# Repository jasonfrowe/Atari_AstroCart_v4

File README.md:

# AstroCart V4: an Atari 7800 multicart on a Tang Nano 9K

AstroCart is a cartridge for the Atari 7800 built around a Sipeed Tang Nano
9K FPGA board. It starts in a menu, lists the `.a78` files on a microSD
card, and runs the one you pick. It also has a High Score Cart, POKEY sound,
and a fixed-point math unit for new programs.

It runs on the AstroCart_V2 circuit board with two hand modifications
([docs/HARDWARE.md](docs/HARDWARE.md)); the next board revision is in
[pcb/](pcb/README.md).

| | |
|---|---|
| [docs/MATHUNIT.md](docs/MATHUNIT.md) | the math unit: registers, accuracy, examples, demos |
| [docs/HARDWARE.md](docs/HARDWARE.md) | the board, the two modifications, pins |
| [docs/DEVELOPMENT.md](docs/DEVELOPMENT.md) | how it works inside, and the history of getting it to work |
| [pcb/README.md](pcb/README.md) | the KiCad project and the changes for the next board |

## What it does

* **Menu.** Browses the card's directories; file names are the titles.
  Up / down move, left / right page, fire opens a directory or starts a
  game. Two lines show the selected file's title, size, mapper, POKEY and TV
  system from its header.
* **SD card.** FAT32, with or without a partition table (MBR or GPT), long
  file names, any directory depth.
* **Cart types**, chosen from the `.a78` header:
  * linear ROM, 8K to 48K, with or without 16K RAM at `$4000`
  * SuperGame up to 512K: plain, with RAM, or with ROM at `$4000`
  * SuperGame up to 255 banks (4 MB), for the 528K and 1024K carts
  * Absolute (F-18 Hornet)
  * Activision (Double Dragon, Rampage), both dump orders
  * mirror RAM
* **POKEY** at `$4000`, `$0450`, `$0800` or `$0440`, and two POKEYs at
  `$0450` + `$0440`.
* **High Score Cart.** Its ROM and RAM come from the card, and the scores are
  written back to the card.
* **Math unit.** For programs written for this cart: 16 x 16 multiply,
  32 / 16 divide, square root, a 32-bit accumulator, a random byte, and a
  trig block (turn a vector by an angle; the angle and length of a vector).
  See [docs/MATHUNIT.md](docs/MATHUNIT.md).
* **Loading over USB.** A game can be sent straight from a computer instead
  of from the card, with bus statistics and a bus trace for debugging.

## What it does not do

* **Other cart hardware:** banked RAM, SOUPER, banksets, YM2151, COVOX and
  the XM are not implemented. Such a file shows NOT SUPPORTED in the menu.
* **Return to the menu from a game.** The way back is to power-cycle the
  FPGA: console off and USB unplugged, or reload the bitstream. A console
  power cycle alone restarts the game if USB keeps the FPGA running.
* **Saves** other than the High Score Cart's.
* **exFAT.** Cards over 32 GB usually come formatted that way; reformat
  them as FAT32.
* **More than 255 entries in one directory.** The first 255 found are shown.
  Titles are cut to 32 characters.
* **PAL** has not been tried: all testing was with NTSC files.
* **POKEY** is the sound half of the chip only, and its pitch has not been
  compared against a real one.

## What you need

To use it:

* An AstroCart_V2 board with the two modifications in
  [docs/HARDWARE.md](docs/HARDWARE.md), and a Tang Nano 9K.
* A microSD card, FAT32.
* [openFPGALoader](https://github.com/trabucayre/openFPGALoader) to put the
  bitstream on the Tang Nano (`brew install openfpgaloader` on a Mac), and a
  USB-C cable.
* A bitstream: `devcart.fs` from this repository's GitHub releases, or built
  as below.

To build it and to work on it:

| Software | Used for | Where the scripts look |
|---|---|---|
| [Gowin IDE](https://www.gowinsemi.com/en/support/download_eda/) (Education edition is enough for the GW1NR-9) | the bitstream | `GOWIN_BIN`, default `/Applications/GowinIDE.app/Contents/Resources/Gowin_EDA/IDE/bin` |
| [7800basic](https://github.com/7800-devtools/7800basic) (a release; it includes `dasm`) | the menu ROM, the demos, the math self-test | `bas7800dir`, default `~/Software/Atari7800/7800basic` |
| Python 3 | every tool in `tools/` (standard library only) | `python3` |
| openFPGALoader | loading and flashing | `openFPGALoader` |
| [Verilator](https://verilator.org) 5 and a C++ compiler | the simulations in `sim/` | `verilator` |
| The [a7800 fork](https://github.com/jasonfrowe/a7800) (MAME-based, with the math unit) | running math-unit programs in an emulator; the demos' and self-test's `run_emu.sh` | `A7800`, default `~/Software/a7800/mame64` |
| [KiCad](https://www.kicad.org) 9 | the board in `pcb/` | |

Only the first four are needed to build and load the cart. The serial tools
use a POSIX serial port (macOS or Linux).

## Getting started

1. **Put the bitstream in the Tang Nano's flash** (once; console off):

   ```bash
   openFPGALoader -b tangnano9k -f devcart.fs
   ```

2. **Prepare the card.** Copy `.a78` files (with their 128-byte headers)
   anywhere on a FAT32 card, in any directories.

3. **For high scores**, add the High Score Cart's two files. You supply the
   HSC ROM as an `.a78` file (128 + 4096 bytes):

   ```bash
   python3 tools/mkhsc.py "High Score Cartridge.a78" OUTDIR
   ```

   and copy `OUTDIR/ASTROCART` to the root of the card. It holds `HSC.A78`
   (the ROM) and `HSC.SAV` (the scores, 2K). An existing `HSC.SAV` is kept.

4. **Card in the Tang Nano, cart in the console, power on.** The menu shows
   "READING THE SD CARD", then the root directory.

LEDs on the Tang Nano (lit = on): 0 heartbeat, 1 cart enabled, 2 loading,
3 HALT pulled recently, 4 PHI2 activity, 5 HALT (DMA) activity.

## Building

```bash
./build.sh                    # build the menu ROM and the bitstream
./build.sh sram               # build, then load into the FPGA's SRAM
./build.sh flash              # build, then write to the FPGA's flash
./build.sh sram  --no-build   # load the bitstream that is already built
./build.sh flash --no-build
```

* **SRAM** is for trying a build: a few seconds, and gone when the FPGA
  loses power (USB unplugged and console off). The FPGA then starts from
  whatever is in flash.
* **Flash** is for the build to keep: loaded at every power-on, so the cart
  works without USB. Writing takes about half a minute.
* Either way the cart restarts in the menu, so switch the console off first.

The bitstream is `hw/devcart/build/impl/pnr/devcart.fs`. The build tries
placement seeds until one meets timing (a few minutes each), because the
FPGA is nearly full; if none does, it removes the bitstream instead of
leaving a bad one. `SEEDS="3 4 5" ./build.sh` chooses the seeds.

The steps by hand:

```bash
menu/build.sh                 # 7800basic -> menu/build/menu.bin (goes into the bitstream)
hw/devcart/build_clean.sh     # Gowin synthesis, place and route, seed sweep
openFPGALoader -b tangnano9k    hw/devcart/build/impl/pnr/devcart.fs    # SRAM
openFPGALoader -b tangnano9k -f hw/devcart/build/impl/pnr/devcart.fs    # flash
```

## Loading a cart over USB: devcart.py

`tools/devcart.py` talks to the cart over the Tang Nano's USB serial port
(230400 baud; it finds `/dev/cu.usbserial-*1` by itself, or `--port PATH`).
It sends a game from the computer, without the SD card:

```bash
python3 tools/devcart.py info GAME.a78     # how the header would be mapped; nothing is sent
```

1. Console **off**, USB connected, bitstream running.
2. `python3 tools/devcart.py load GAME.a78`
   The file goes into the cart's memory, is read back and compared, and the
   cart is switched on with that game in place of the menu. A 32K game
   takes about 2 seconds; the upload runs at about 23 kB a second.
3. Console on: the game starts. To change game: console off, `load` again.

The game stays loaded for as long as the FPGA has power, so the console can
be switched off and on. The math unit is enabled from the header just as the
menu does it. `load --no-halt` switches banks without stopping the 6502, as
games started from the menu do; without it the older stop-and-copy method is
used.

While a game runs:

```bash
python3 tools/devcart.py ident             # is the cart there? -> AC78V4 <enabled> <trace> <bank>
python3 tools/devcart.py stats             # bank switches, POKEY writes, High Score Cart saves, ...
python3 tools/devcart.py trace arm now     # record 512 bus cycles from now
python3 tools/devcart.py trace arm bank    #   ... or from the next bank switch
python3 tools/devcart.py trace dump FILE
python3 tools/devcart.py off               # stop driving the bus
```

With the console off, the card can be exercised from the computer the way
the menu does it:

```bash
python3 tools/devcart.py sd ls [DIR]                           # a directory, as the menu lists it
python3 tools/devcart.py sd load DIR/NAME --check GAME.a78     # load, start, compare with a local copy
```

`python3 tools/devcart.py --help` lists everything.

## Programs for the math unit

A program asks for the math unit with three bytes in its `.a78` header
(`tools/a78math.py FILE.a78` sets them). The definition, with examples, is
[docs/MATHUNIT.md](docs/MATHUNIT.md). The a7800 fork implements the same
unit bit for bit, so such programs can be developed in the emulator.

Five demos, in 7800basic with assembly for the arithmetic; each directory
has a README, and `demos/NAME/build.sh` makes `demos/NAME/build/NAME.a78`:

| | |
|---|---|
| `demos/galton` | a Galton board: balls, pegs and a bell curve |
| `demos/nbody` | gravity between up to four bodies, four scenarios |
| `demos/gas` | twelve discs in a box, and their speed distribution |
| `demos/spin` | a 3D point cloud turning in perspective (trig block) |
| `demos/orbit` | a game for two: launch probes at a moon round a star (trig block) |

`tests/mathtest` is the unit's self-test cart: 13,130 register checks against
the reference model, green screen for a pass.

## Tests without a console

```bash
(cd sim/math && make)              # the math unit's Verilog against its reference model
(cd sim/devcart && make)           # the cart: load, mappers, 6502 and MARIA-style traffic
(cd sim/multicart && make run)     # menu + SD card model + every mapper, 6502 code included (15 minutes)
(cd sim/pokey && make)             # POKEY
tests/mathtest/run_emu.sh          # the math self-test in the a7800 fork
```

`sim/multicart` loads the carts in `tests/carts`, and adds more cases if
Trebor's 7800 ROM PROPack is at `$PROPACK` (default
`~/Downloads/Trebors 7800 ROM PROPack v8_17`).

## Layout

```
rtl/cart/cart_bus.v      the 7800 bus: address filter, BRAM slots, write capture, bank switches
rtl/dev/devcart_top.v    top level: USB loader and commands, PSRAM-to-slot copy, menu registers
rtl/psram/               PSRAM controller, and both dies raced
rtl/sd/sd_spi.v          SD card, SPI mode
rtl/audio/               POKEY (sound) and PWM output
rtl/math/astromath.v     the math unit
menu/                    the menu: menu.bas (7800basic), fat.asm (card, FAT32, loader, launch)
hw/devcart/              pin constraints and the Gowin build
tools/                   devcart.py (USB), mkhsc.py, a78math.py, mkfat32.py (card images for tests)
sim/                     Verilator testbenches; sim/math/astromath.h is the math unit's reference model
tests/mathtest/          the math unit's self-test cart
tests/carts/             directory for test cart images (see tests/carts/README.md)
demos/                   programs for the math unit
lab/psram_lab/           the bitstream that characterised the PSRAM
pcb/                     KiCad project for the next board revision
docs/                    MATHUNIT, HARDWARE, DEVELOPMENT
```

## Licence

AstroCart V4 is free software under the GNU General Public License, version
3 or (at your option) any later version; see [LICENSE](LICENSE). It comes
with no warranty.

That covers what was written for this project: the Verilog in `rtl/`, the
menu, the tools, the simulations, the demos, the documents and the board in
`pcb/`. It does not cover third-party cart images
([tests/carts/README.md](tests/carts/README.md)), nor the pieces below that
came from elsewhere under their own terms.

## Credits

* **PSRAM controller.** `rtl/psram/psram_ll.v` is derived from Feng Zhou's
  (nand2mario) [PSRAM/HyperRAM controller for the Tang Nano
  9K](https://github.com/zf3/psram-tang-nano-9k), Apache License 2.0.
* **6502 for the simulation.** `sim/third_party/fake6502` is Fake6502 by Mike
  Chambers as modified by the [LLVM-MOS
  project](https://github.com/llvm-mos/llvm-mos-sdk), Apache License 2.0
  with LLVM exceptions; an unmodified copy, used only by `sim/multicart`.
* **7800basic** by Michael Saarna, derived from Fred Quimby's batari Basic:
  the menu and the demos are written in it, and assembled with the `dasm`
  it ships. `menu/gfx/menufont.png` is the `atascii.png` font from its
  samples. The built menu ROM inside the bitstream contains 7800basic's
  runtime (its 6502 code is CC0).
* **a7800**, the MAME-based Atari 7800 emulator by Mike Saarna and Robert
  Tuccitto: the mapper definitions here follow its source, and the
  [fork](https://github.com/jasonfrowe/a7800) with the math unit is how
  programs for it are developed.
* **POKEY.** `rtl/audio/pokey.v` was written for this project from the
  description in Avery Lee's Altirra Hardware Reference Manual.
* **Trebor's 7800 ROM PROPack** supplied the test files for the mappers
  beyond the eight in `tests/carts`.
* **Tools:** the Gowin EDA software, Verilator, openFPGALoader, KiCad.

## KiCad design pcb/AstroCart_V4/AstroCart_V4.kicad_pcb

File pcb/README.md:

# AstroCart PCB

`AstroCart_V4/` is the KiCad project for the V4 board revision. It builds
upon the original AstroCart_V2 board that development was done on,
incorporating the required hardware bodges and an audio filter improvement.

## Changes implemented in V4

The V2 prototype board required hand modifications to operate reliably. These
modifications, along with an audio low-pass filter component update, have been
incorporated into the V4 schematic and PCB layout:

| | V2 as drawn | V4 implementation |
|---|---|---|
| 1 | Q1 (BSS138) drain on cartridge pin 31 (`IRQ`) | Q1 drain routed to cartridge **pin 2 (`HALT`)**. In schematic/PCB, gate net is `/Q_HALT` (Tang Nano pin 83). Allows the FPGA to pull HALT low to stop the 6502 (e.g., during `devcart.py load`). |
| 2 | Q1 gate had no pull-down resistor (floated during FPGA configuration) | Added **R5 (10 kΩ, 0805)** from Q1 gate (`/Q_HALT`) to GND. Prevents Q1 from conducting and asserting HALT during console power-on reset. |
| 3 | Audio low-pass filter: R1 = 1 kΩ, C8 = 0.1 µF (cutoff ~1.6 kHz) | Updated **C8 to 10 nF** (with R1 = 1 kΩ), raising the low-pass cutoff to **~16 kHz**. Keeps audio clear without attenuating audible high frequencies while still filtering the 264 kHz PWM carrier. |

Background context, timing observations, and startup symptoms without the gate
pull-down are documented in [docs/HARDWARE.md](../docs/HARDWARE.md).

Since build 4, the cart does not pull HALT for games started from the menu
(bank switches are handled without stopping the 6502). Only `devcart.py load`
without `--no-halt` uses Q1. It remains on the board because it costs minimal
parts and provides the only mechanism for the cart to stop the 6502.

## Remaining suggestions for future revisions

Read from the schematic and from development findings. None of these are
strictly necessary for the cart to function as intended:

1. **A button for "back to the menu".** The only way back today is to
   power-cycle the FPGA. A push button on a free 3.3 V pin (Tang Nano pins
   68-75 are unconnected), reachable with the cart in the console, would let
   the bitstream do it. The Tang Nano's own buttons S1 and S2 (pins 4 and 3)
   could serve if they can be reached in the shell; a button on the board
   edge is easier to press. Needs RTL as well.
2. **A14 and A15 through U4.** A0-A13 come through SN74LVC245s on 3.3 V
   banks, A14 and A15 through the SN74LVC8T245 (U5) on the 1.8 V bank, so the
   two top address lines have different delays and thresholds from the rest;
   the bus logic waits for two equal samples because of it. U4 has two unused
   channels (A1/B1, A2/B2, inputs tied to ground now) and the Tang Nano has
   free 3.3 V pins, so all sixteen could take the same path. This changes
   the pin constraints, and the present arrangement works; do it only if the
   board is being re-routed there anyway.
3. **IRQ, if it is ever wanted** (POKEY interrupts, for example): its own
   BSS138 with a gate pull-down, on a free pin. U5's eighth channel (A8/B8)
   is free if the cart should also read the line.
4. **Test points** for PHI2, HALT, R/W, A15 and a data line at the cartridge
   edge: every timing question in this project was answered with a probe on
   those.

Things looked at and left alone: D2 (SS14) keeps USB power from back-feeding
the console; U5's B side and the 1.8 V regulator run from the console's 5 V
only, and the SN74LVC8T245 isolates its A side when that is off, so
USB-only operation on the bench is fine; R2 holds the data-bus driver off
until the FPGA is configured.

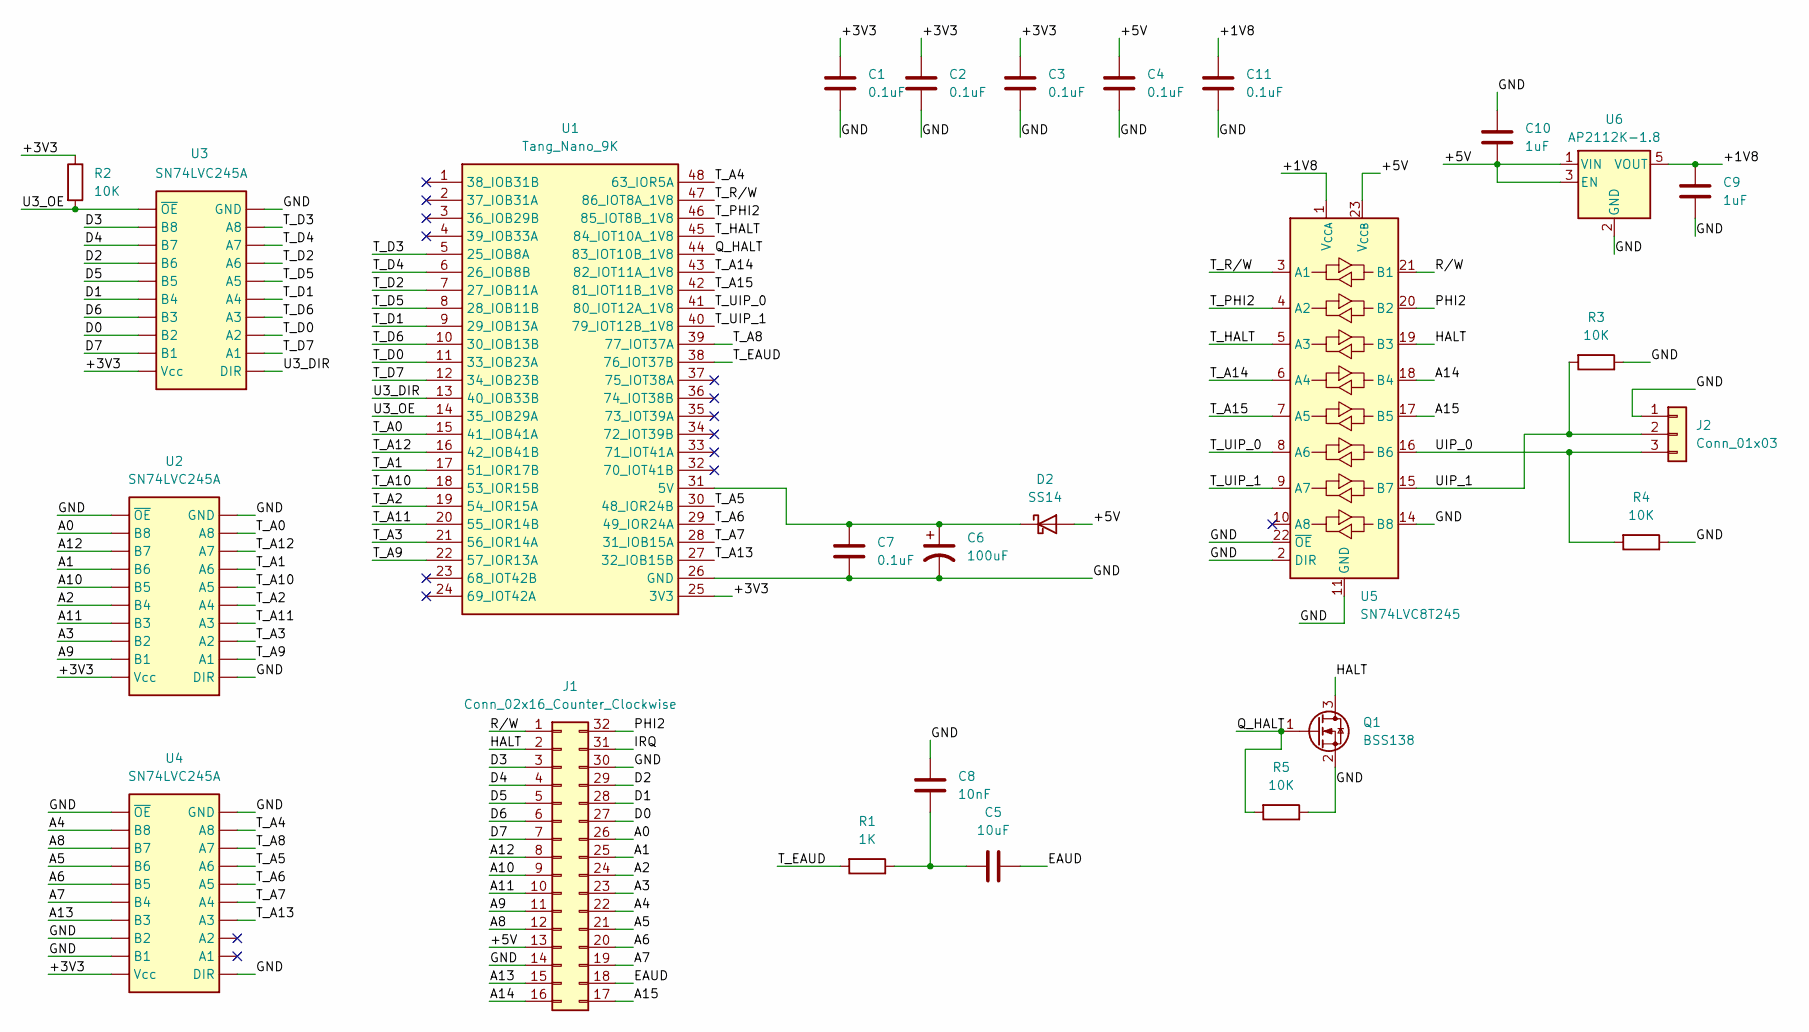
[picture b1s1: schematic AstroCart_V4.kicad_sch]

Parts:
C1, C2, C3, C4, C7, C11: 0.1uF; C_0805_2012Metric_Pad1.18x1.45mm_HandSolder
C5: 10uF; C_0805_2012Metric_Pad1.18x1.45mm_HandSolder
C6: 100uF; CP_Radial_D6.3mm_P2.50mm
C8: 10nF; C_0805_2012Metric_Pad1.18x1.45mm_HandSolder
C9, C10: 1uF; C_0805_2012Metric_Pad1.18x1.45mm_HandSolder
D2: SS14; D_SMA
J1: Conn_02x16_Counter_Clockwise; A7800
J2: Conn_01x03; JST_XH_B3B-XH-A_1x03_P2.50mm_Vertical
Q1: BSS138; SOT-23
R1: 1K; R_0805_2012Metric_Pad1.20x1.40mm_HandSolder
R2, R3, R4, R5: 10K; R_0805_2012Metric_Pad1.20x1.40mm_HandSolder
U1: Tang_Nano_9K; DIP-48_TangNano9K
U2, U3, U4: SN74LVC245A; SOIC-20W_7.5x12.8mm_P1.27mm
U5: SN74LVC8T245; SOIC-24W_7.5x15.4mm_P1.27mm
U6: AP2112K-1.8; SOT-23-5

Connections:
/+1V8: C9.2, C11.1, U5.1 (V_{CCA}), U6.5 (VOUT)
/+3V3: C1.1, C2.1, C3.1, R2.1, U1.25 (3V3), U2.20 (Vcc), U3.20 (Vcc), U4.20 (Vcc)
/+5V: C4.1, C10.1, D2.2 (A), J1.13, U5.23 (V_{CCB}), U5.24 (V_{CCB}), U6.1 (VIN), U6.3 (EN)
/A0: J1.26, U2.11 (B8)
/A1: J1.25, U2.13 (B6)
/A2: J1.24, U2.15 (B4)
/A3: J1.23, U2.17 (B2)
/A4: J1.22, U4.11 (B8)
/A5: J1.21, U4.13 (B6)
/A6: J1.20, U4.14 (B5)
/A7: J1.19, U4.15 (B4)
/A8: J1.12, U4.12 (B7)
/A9: J1.11, U2.18 (B1)
/A10: J1.9, U2.14 (B5)
/A11: J1.10, U2.16 (B3)
/A12: J1.8, U2.12 (B7)
/A13: J1.15, U4.16 (B3)
/A14: J1.16, U5.18 (B4)
/A15: J1.17, U5.17 (B5)
/D0: J1.27, U3.17 (B2)
/D1: J1.28, U3.15 (B4)
/D2: J1.29, U3.13 (B6)
/D3: J1.3, U3.11 (B8)
/D4: J1.4, U3.12 (B7)
/D5: J1.5, U3.14 (B5)
/D6: J1.6, U3.16 (B3)
/D7: J1.7, U3.18 (B1)
/EAUD: C5.1, J1.18
/GND: C1.2, C2.2, C3.2, C4.2, C6.2, C7.2, C8.1, C9.1, C10.2, C11.2, J1.14, J1.30, J2.1, Q1.2 (S), R3.1, R4.1, R5.1, U1.26 (GND), U2.1 (DIR), U2.10 (GND), U2.19 (~OE), U3.10 (GND), U4.1 (DIR), U4.10 (GND), U4.17 (B2), U4.18 (B1), U4.19 (~OE), U5.2 (DIR), U5.11 (GND), U5.12 (GND), U5.13 (GND), U5.14 (B8), U5.22 (~OE), U6.2 (GND)
/HALT: J1.2, Q1.3 (D), U5.19 (B3)
/IRQ: J1.31
/PHI2: J1.32, U5.20 (B2)
/Q_HALT: Q1.1 (G), R5.2, U1.44 (83_IOT10B_1V8)
/R/W: J1.1, U5.21 (B1)
/T_A0: U1.15 (41_IOB41A), U2.9 (A8)
/T_A1: U1.17 (51_IOR17B), U2.7 (A6)
/T_A2: U1.19 (54_IOR15A), U2.5 (A4)
/T_A3: U1.21 (56_IOR14A), U2.3 (A2)
/T_A4: U1.48 (63_IOR5A), U4.9 (A8)
/T_A5: U1.30 (48_IOR24B), U4.7 (A6)
/T_A6: U1.29 (49_IOR24A), U4.6 (A5)
/T_A7: U1.28 (31_IOB15A), U4.5 (A4)
/T_A8: U1.39 (77_IOT37A), U4.8 (A7)
/T_A9: U1.22 (57_IOR13A), U2.2 (A1)
/T_A10: U1.18 (53_IOR15B), U2.6 (A5)
/T_A11: U1.20 (55_IOR14B), U2.4 (A3)
/T_A12: U1.16 (42_IOB41B), U2.8 (A7)
/T_A13: U1.27 (32_IOB15B), U4.4 (A3)
/T_A14: U1.43 (82_IOT11A_1V8), U5.6 (A4)
/T_A15: U1.42 (81_IOT11B_1V8), U5.7 (A5)
/T_D0: U1.11 (33_IOB23A), U3.3 (A2)
/T_D1: U1.9 (29_IOB13A), U3.5 (A4)
/T_D2: U1.7 (27_IOB11A), U3.7 (A6)
/T_D3: U1.5 (25_IOB8A), U3.9 (A8)
/T_D4: U1.6 (26_IOB8B), U3.8 (A7)
/T_D5: U1.8 (28_IOB11B), U3.6 (A5)
/T_D6: U1.10 (30_IOB13B), U3.4 (A3)
/T_D7: U1.12 (34_IOB23B), U3.2 (A1)
/T_EAUD: R1.2, U1.38 (76_IOT37B)
/T_HALT: U1.45 (84_IOT10A_1V8), U5.5 (A3)
/T_PHI2: U1.46 (85_IOT8B_1V8), U5.4 (A2)
/T_R/W: U1.47 (86_IOT8A_1V8), U5.3 (A1)
/T_UIP_0: U1.41 (80_IOT12A_1V8), U5.8 (A6)
/T_UIP_1: U1.40 (79_IOT12B_1V8), U5.9 (A7)
/U3_DIR: U1.13 (40_IOB33B), U3.1 (DIR)
/U3_OE: R2.2, U1.14 (35_IOB29A), U3.19 (~OE)
/UIP_0: J2.3, R4.2, U5.16 (B6)
/UIP_1: J2.2, R3.2, U5.15 (B7)
unnamed: C5.2, C8.2, R1.1
unnamed: C6.1, C7.1, D2.1 (K), U1.31 (5V)

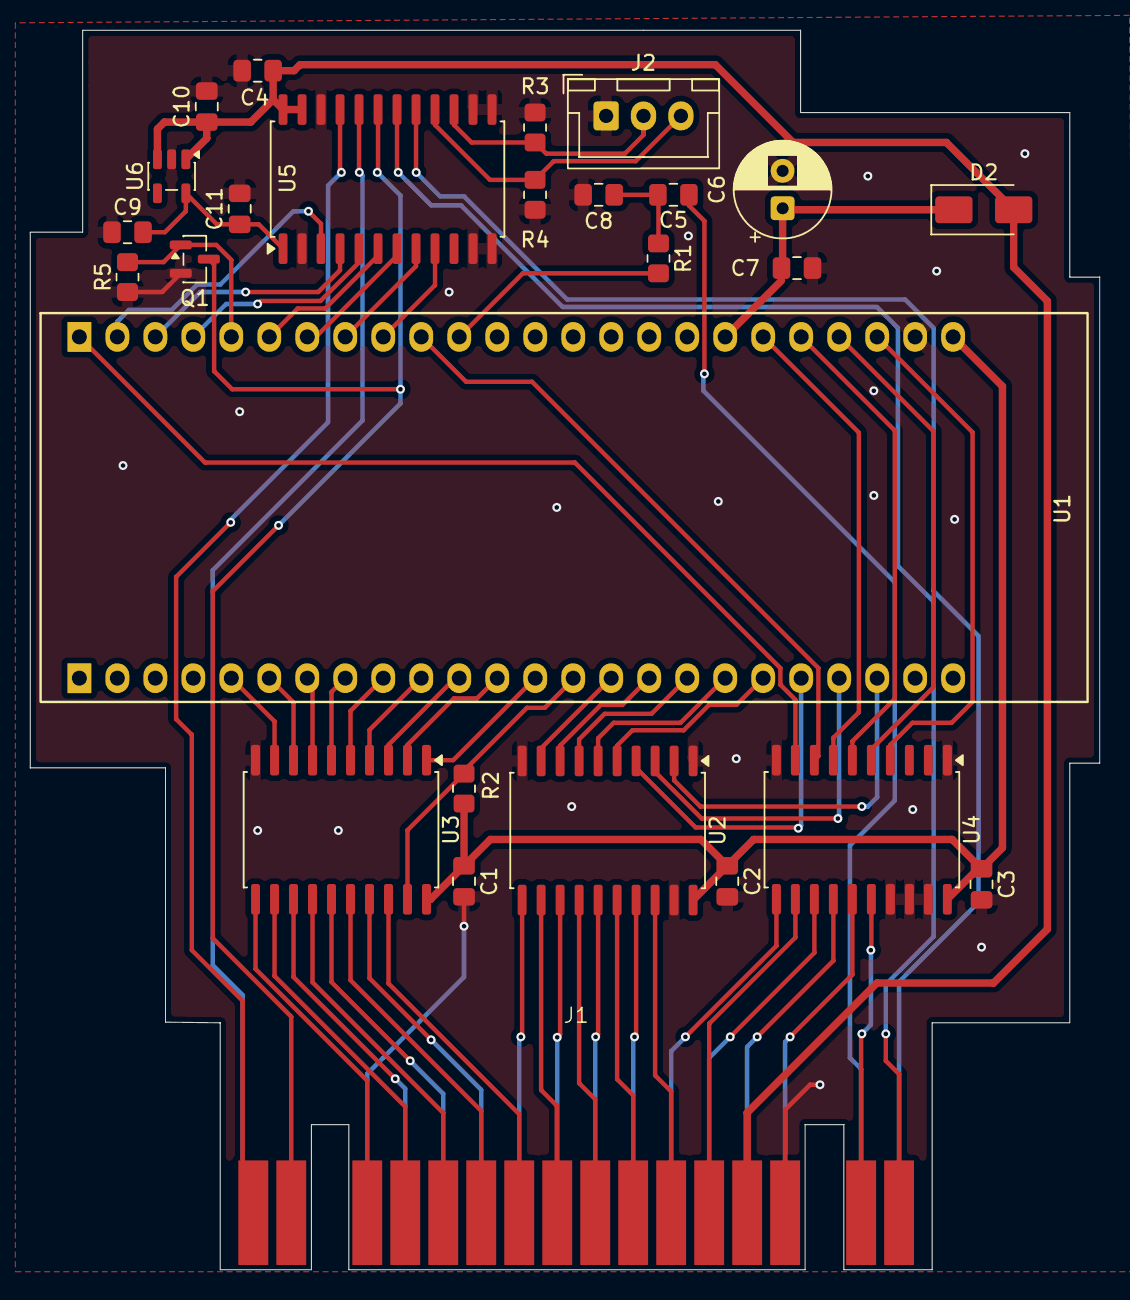
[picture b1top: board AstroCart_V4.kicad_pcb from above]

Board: 2 copper layers, 71.5 x 82.9 mm, 26 parts (0 on the bottom side), 69 nets.
